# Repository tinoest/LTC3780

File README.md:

# LTC3780
BuckBoostConverter

Circuit for the LTC3789 Buck/Boost Converter in KiCAD.

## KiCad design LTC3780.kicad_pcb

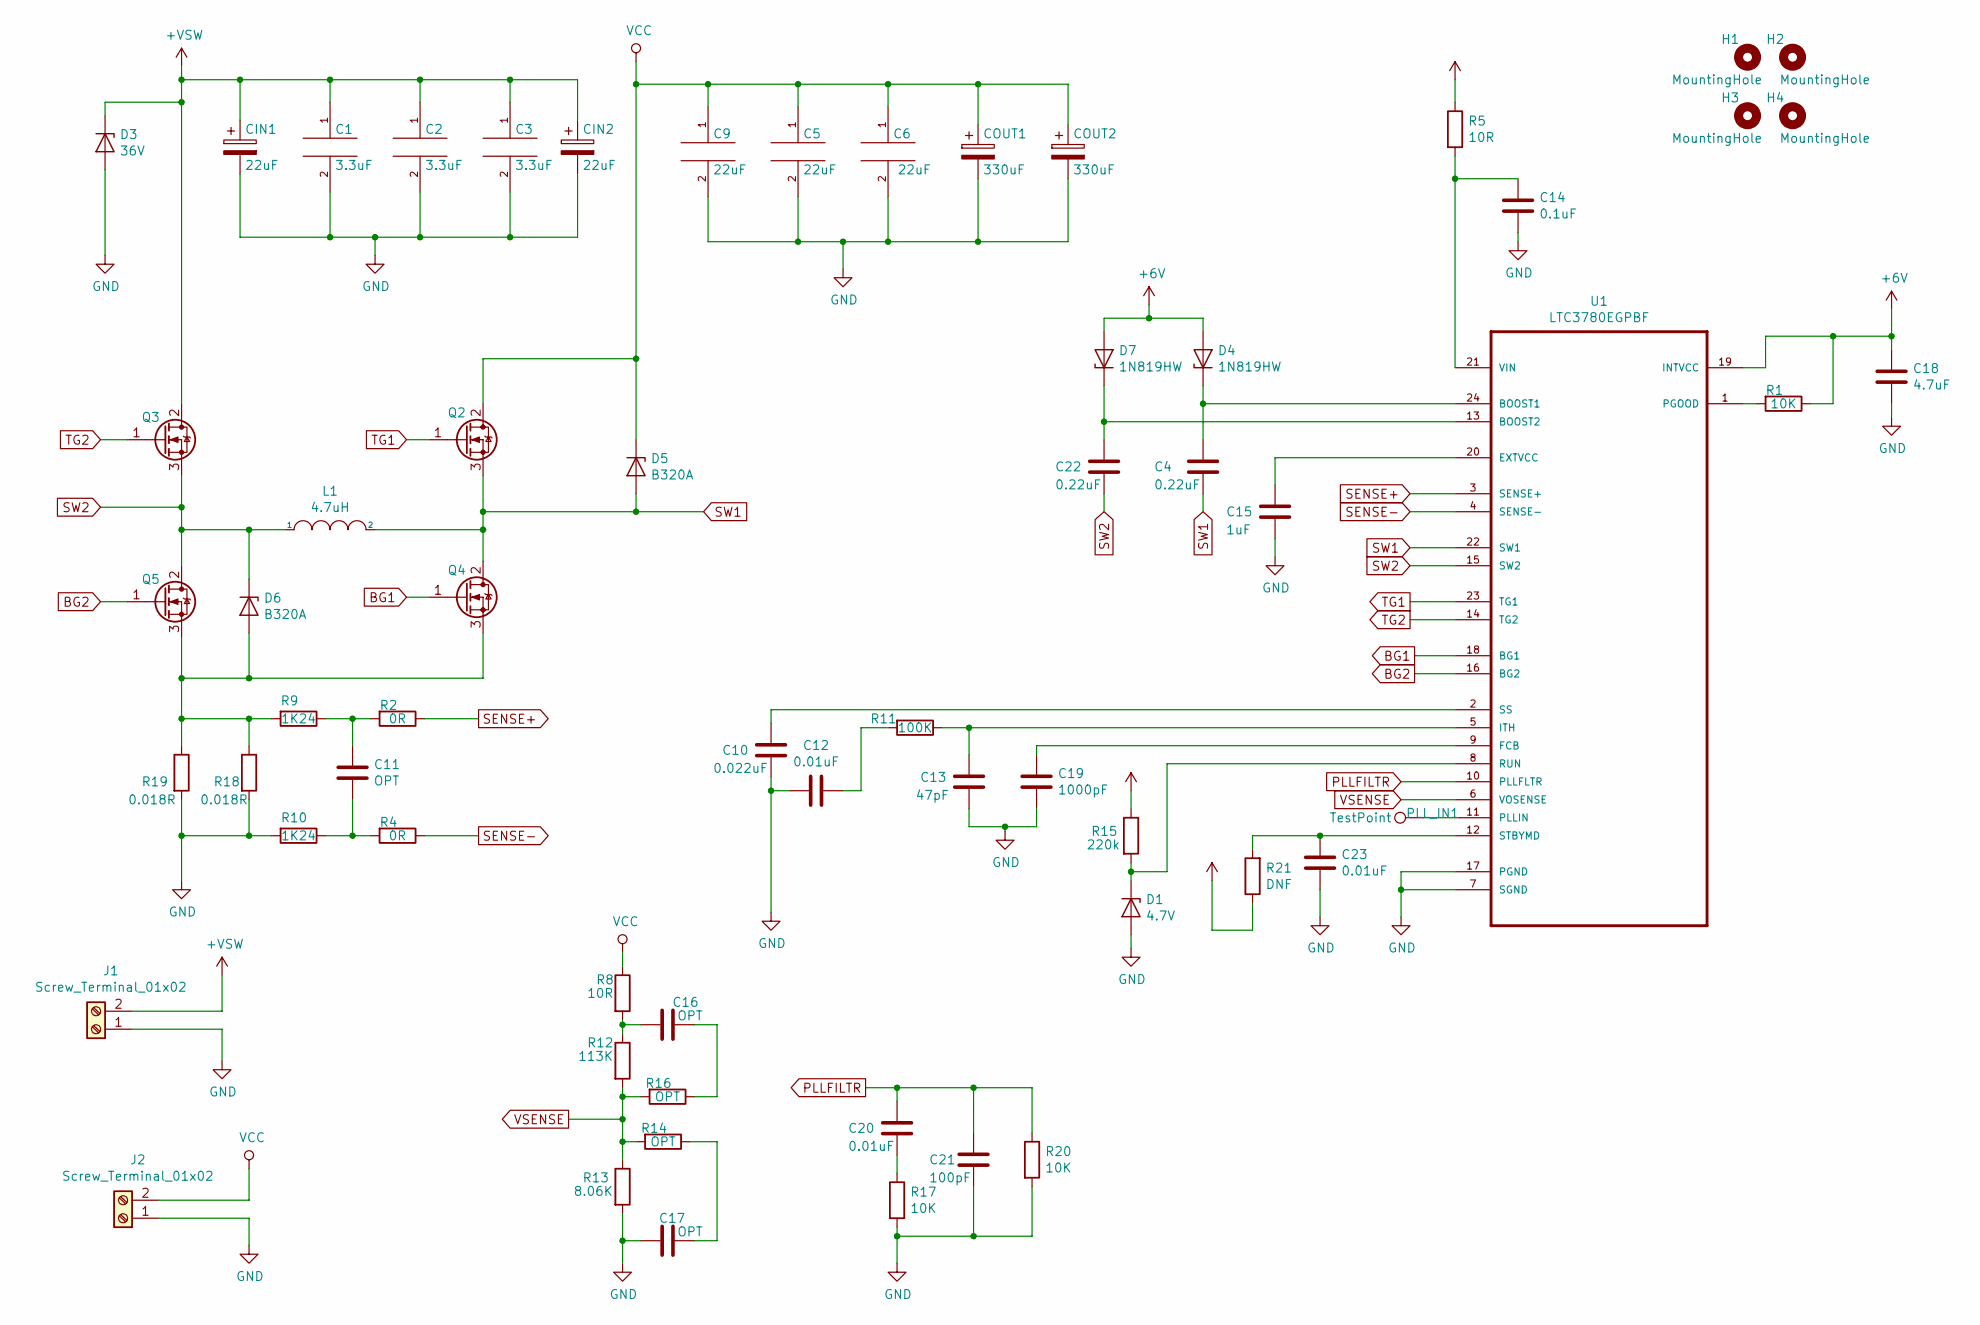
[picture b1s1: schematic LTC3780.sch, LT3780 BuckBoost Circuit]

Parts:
C1, C2, C3: 3.3uF; C_0603_HandSoldering
C4, C22: 0.22uF; C_0603_HandSoldering
C5, C6, C9: 22uF; C_0603_HandSoldering
C10: 0.022uF; C_0603_HandSoldering
C11, C16, C17: OPT; C_0603_HandSoldering
C12, C20, C23: 0.01uF; C_0603_HandSoldering
C13: 47pF; C_0603_HandSoldering
C14: 0.1uF; C_0603_HandSoldering
C15: 1uF; C_0603_HandSoldering
C18: 4.7uF; C_0603_HandSoldering
C19: 1000pF; C_0603_HandSoldering
C21: 100pF; C_0603_HandSoldering
CIN1, CIN2: 22uF; CP_Elec_8x6.7
COUT1, COUT2: 330uF; CP_Elec_8x10.5
D1: 4.7V; D_SOD-323_HandSoldering
D3: 36V; D_SOT-23_ANK
D4, D7: 1N819HW; D_SOD-123
D5, D6: B320A; D_SMA_Handsoldering
H1, H2, H3, H4: MountingHole; MountingHole_4mm
J1, J2: Screw_Terminal_01x02; JST_VH_B2P-VH_2x3.96mm_Vertical
L1: 4.7uH; Inductor_Wurth_MAPI-4020
PLL_IN1: TestPoint; Measurement_Point_Square-SMD-Pad_Small
Q2, Q3, Q4, Q5: IPD100N04S402ATMA1; TO-252-2
R1, R17, R20: 10K; R_0603_HandSoldering
R2, R4: 0R; R_0603_HandSoldering
R5, R8: 10R; R_0603_HandSoldering
R9, R10: 1K24; R_0603_HandSoldering
R11: 100K; R_0603_HandSoldering
R12: 113K; R_0603_HandSoldering
R13: 8.06K; R_0603_HandSoldering
R14, R16: OPT; R_0603_HandSoldering
R15: 220k; R_0603_HandSoldering
R18, R19: 0.018R; R_2512_HandSoldering
R21: DNF; R_0603_HandSoldering
U1: LTC3780EGPBF; SOP65P780X200-24N

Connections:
+6V: C18.1, D4.2 (A), D7.2 (A), R1.1, U1.19 (INTVCC)
+VSW: C1.1, C2.1, C3.1, CIN1.1, CIN2.1, D3.1 (K), J1.2, Q3.2, R5.1, R15.1, R21.1
BG1: Q4.1, U1.18 (BG1)
BG2: Q5.1, U1.16 (BG2)
GND: C1.2, C2.2, C3.2, C5.2, C6.2, C9.2, C10.2, C12.2, C13.2, C14.2, C15.1, C17.2, C18.2, C19.2, C21.2, C23.2, CIN1.2, CIN2.2, COUT1.2, COUT2.2, D1.2 (A), D3.2 (A), J1.1, J2.1, R10.2, R13.2, R17.2, R18.2, R19.2, R20.2, U1.7 (SGND), U1.17 (PGND)
unnamed: C4.1, D4.1 (K), U1.24 (BOOST1)
unnamed: C10.1, U1.2 (SS)
unnamed: C11.1, R2.2, R9.1
unnamed: C11.2, R4.2, R10.1
unnamed: C12.1, R11.2
unnamed: C13.1, R11.1, U1.5 (ITH)
unnamed: C14.1, R5.2, U1.21 (VIN)
unnamed: C15.2, U1.20 (EXTVCC)
unnamed: C16.1, R16.1
unnamed: C16.2, R8.2, R12.1
unnamed: C17.1, R14.1
unnamed: C19.1, U1.9 (FCB)
unnamed: C20.2, R17.1
unnamed: C22.1, D7.1 (K), U1.13 (BOOST2)
unnamed: C23.1, R21.2, U1.12 (STBYMD)
unnamed: D1.1 (K), R15.2, U1.8 (RUN)
unnamed: D6.2 (A), Q4.3, Q5.3, R9.2, R18.1, R19.1
unnamed: PLL_IN1.1, U1.11 (PLLIN)
unnamed: R1.2, U1.1 (PGOOD)
PLLFILTR: C20.1, C21.1, R20.1, U1.10 (PLLFLTR)
SENSE+: R2.1, U1.3 (SENSE+)
SENSE-: R4.1, U1.4 (SENSE-)
SW1: C4.2, D5.2 (A), L1.2, Q2.3, Q4.2, U1.22 (SW1)
SW2: C22.2, D6.1 (K), L1.1, Q3.3, Q5.2, U1.15 (SW2)
TG1: Q2.1, U1.23 (TG1)
TG2: Q3.1, U1.14 (TG2)
VCC: C5.1, C6.1, C9.1, COUT1.1, COUT2.1, D5.1 (K), J2.2, Q2.2, R8.1
VSENSE: R12.2, R13.1, R14.2, R16.2, U1.6 (VOSENSE)

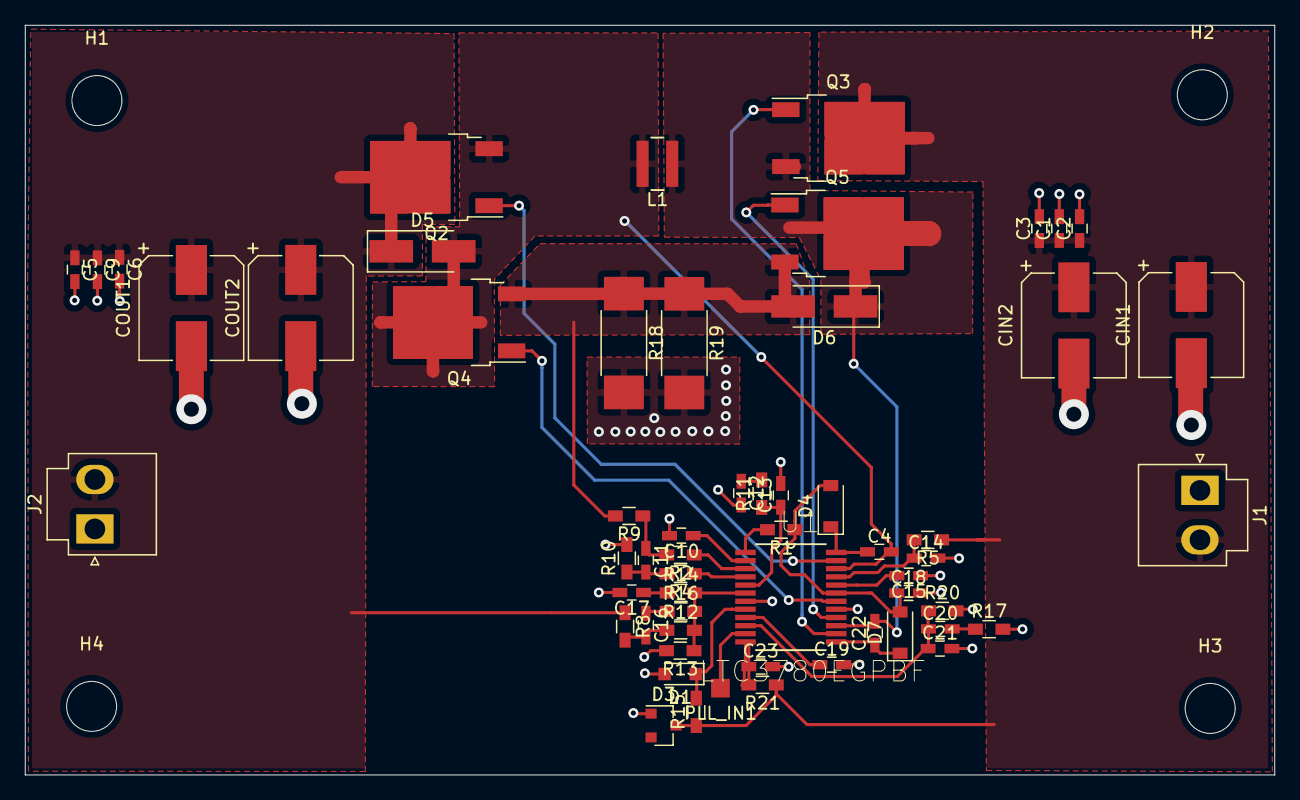
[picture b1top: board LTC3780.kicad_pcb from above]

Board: 2 copper layers, 100.0 x 60.0 mm, 62 parts (0 on the bottom side), 33 nets.

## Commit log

2019-04-12 LTC3780 Schematic
    First pass at the LTC3780 Schematic
2019-04-12 Footprints added
2019-04-12 Added Different Switching MOSFET
2019-04-28 Updated to include connector
2019-04-28 Create LICENSE
2019-04-28 Revert "Delete LTC3780.pro"
    This reverts commit ff6af7f2de91a7127ada6b3708bc609f74e58f3c.
2019-04-28 Updated PCB from Netlist
2019-04-29 Updated with drawing dimensions for board
2019-05-03 Routed and placed some components
2019-05-04 Finished PCB first layout and routing, generated gerber files
2019-05-04 Reduced PCB to 100mm * 60mm and included zip of Gerbers
2019-05-04 Added PDF of schematic
2019-05-11 Updated PCB, added routing holes and reordered some components.
2019-05-11 Added additional Capacitor, corrected drill sizes
2019-06-07 Updating to latest version tidied routing
